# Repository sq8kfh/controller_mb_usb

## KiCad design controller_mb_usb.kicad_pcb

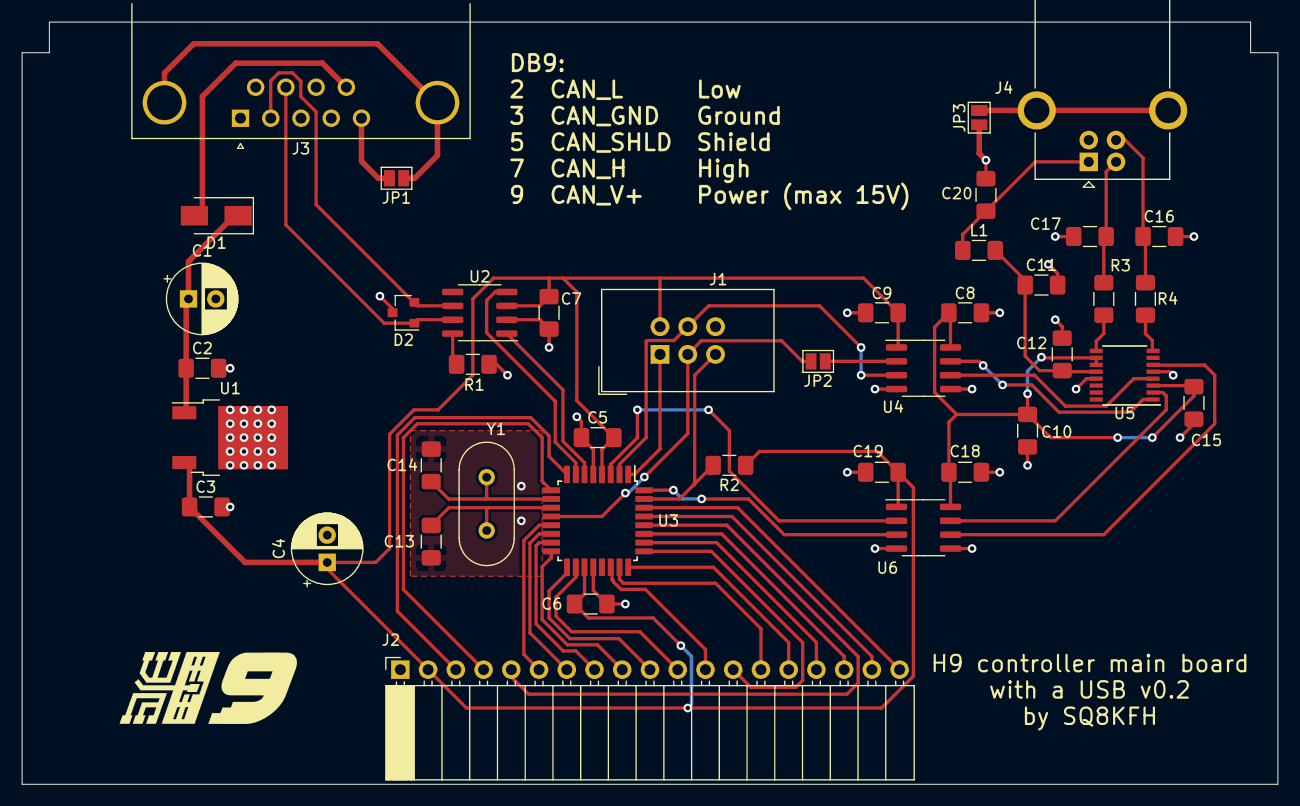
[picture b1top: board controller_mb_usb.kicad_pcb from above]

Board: 2 copper layers, 115.0 x 69.8 mm, 41 parts (0 on the bottom side), 50 nets.

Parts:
C1: 100uF; CP_Radial_D6.3mm_P2.50mm
C2, C3, C5, C6, C7, C8, C9, C12, C15, C18, C19: 100nF; C_1206_3216Metric_Pad1.42x1.75mm_HandSolder
C4: 47uF; CP_Radial_D6.3mm_P2.50mm
C10, C11: 4.7uF; C_1206_3216Metric_Pad1.42x1.75mm_HandSolder
C13, C14: 22pF; C_1206_3216Metric_Pad1.42x1.75mm_HandSolder
C16, C17: 47pF; C_1206_3216Metric_Pad1.42x1.75mm_HandSolder
C20: 10nF; C_1206_3216Metric_Pad1.42x1.75mm_HandSolder
D1: S1A; D_SMA
D2: NUP2105L; SOT-23
J1: AVR-ISP-6; IDC-Header_2x03_P2.54mm_Vertical
J2: Front panel; PinSocket_1x19_P2.54mm_Horizontal
J3: CAN; DSUB-9_Female_Horizontal_P2.77x2.84mm_EdgePinOffset7.70mm_H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
J4: USB_B; USB_B_OST_USB-B1HSxx_Horizontal
JP1, JP3: Shield; SolderJumper-2_P1.3mm_Open_Pad1.0x1.5mm
JP2: Jumper_NC_Small; SolderJumper-2_P1.3mm_Open_Pad1.0x1.5mm
L1: Ferrite Bead; L_1206_3216Metric_Pad1.42x1.75mm_HandSolder
R1: 39k; R_1206_3216Metric_Pad1.42x1.75mm_HandSolder
R2: 10k; R_1206_3216Metric_Pad1.42x1.75mm_HandSolder
R3, R4: 27R; R_1206_3216Metric_Pad1.42x1.75mm_HandSolder
U1: LM78M05; TO-252-2
U2: MCP2551-I-SN; SOIC-8_3.9x4.9mm_P1.27mm
U3: ATmega32M1-AU; TQFP-32_7x7mm_P0.8mm
U4, U6: ADuM121N; SOIC-8_3.9x4.9mm_P1.27mm
U5: FT230XS; SSOP-16_3.9x4.9mm_P0.635mm
Y1: 12MHz; Crystal_HC49-U_Vertical

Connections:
+3V3: C8.2, C10.1, C15.1, C18.2, U4.8, U5.3, U5.10, U5.11, U6.8
+5V: C3.1, C4.1, C5.2, C6.1, C7.2, C9.1, C19.1, J1.2, J2.2, R2.1, U1.3, U2.3, U3.4, U3.19, U4.1, U6.1
/CAN_H: D2.1, J3.7, U2.7
/CAN_L: D2.2, J3.2, U2.6
/CAN_RX: U2.4, U3.7
/CAN_TX: U2.1, U3.6
/CTS: U3.32, U6.3
/D+: C16.1, J4.3, R4.1
/D-: C17.1, J4.2, R3.1
/MISO: J1.1, U3.1
/MOSI(TX): J1.4, U3.2, U4.3
/PB0(MISO): J2.3, U3.8
/PB1(MOSI): J2.4, U3.9
/PB2(INT1): J2.9, U3.16
/PB3: J2.14, U3.23
/PB4: J2.15, U3.24
/PB5(INT2): J2.16, U3.26
/PB6: J2.17, U3.27
/PB7(SCK): J2.5, U3.28
/PC0(INT3): J2.19, U3.30
/PC4: J2.10, U3.17
/PC5: J2.11, U3.18
/PC6: J2.12, U3.22
/PC7(D2A): J2.13, U3.25
/PD0: J2.18, U3.29
/PD5: J2.6, U3.13
/PD6: J2.7, U3.14
/PD7: J2.8, U3.15
/RST: J1.5, R2.2, U3.31
/RTS: U3.3, U6.2
/SCK(RX): J1.3, JP2.2, U3.12
/USB+: R4.2, U5.8
/USB-: R3.2, U5.9
GND: C1.2, C2.2, C3.2, C4.2, C5.1, C6.2, C7.1, C9.2, C13.2, C14.2, C19.2, D2.3, J1.6, J2.1, J3.3, R1.2, U1.2, U2.2, U3.5, U3.20, U4.4, U6.4
GNDD: C8.1, C10.2, C11.2, C12.2, C15.2, C16.2, C17.2, C18.1, C20.2, J4.4, JP3.1, U4.5, U5.5, U5.13, U6.5
unnamed: C1.1, C2.1, D1.1, U1.1
unnamed: C11.1, C12.1, L1.2, U5.12
unnamed: C13.1, U3.11, Y1.1
unnamed: C14.1, U3.10, Y1.2
unnamed: C20.1, J4.1, L1.1
unnamed: D1.2, J3.9
unnamed: J3.0, JP1.1
unnamed: J3.5, JP1.2
unnamed: J4.5, JP3.2
unnamed: JP2.1, U4.2
unnamed: R1.1, U2.8
unnamed: U4.6, U5.4
unnamed: U4.7, U5.1
unnamed: U5.2, U6.7
unnamed: U5.6, U6.6

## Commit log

2020-12-21 v0.1
2020-12-24 Init v0.2
2020-12-24 v0.2
